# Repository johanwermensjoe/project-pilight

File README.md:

# project-pilight
An ambilight clone using Raspberry Pi.

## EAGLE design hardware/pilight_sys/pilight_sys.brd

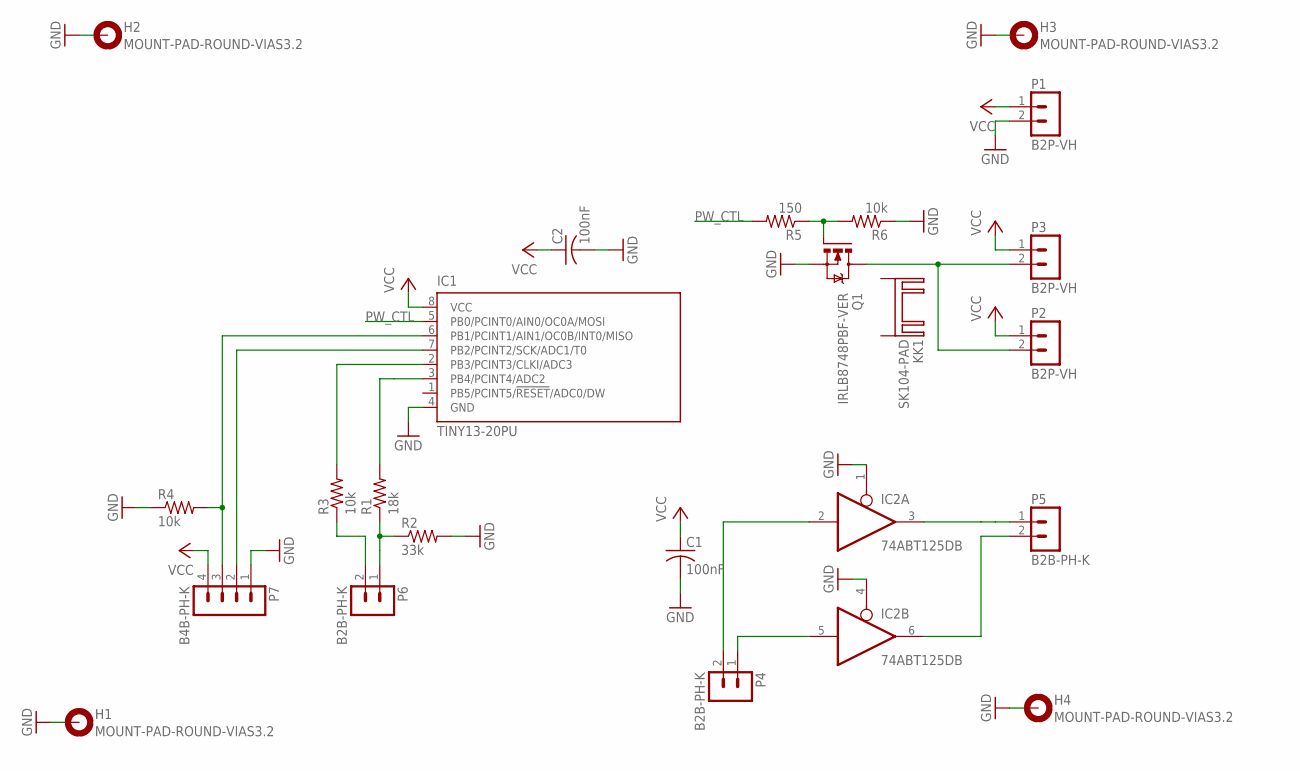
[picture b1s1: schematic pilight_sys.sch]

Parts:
C1, C2: 100nF; C0805
H1, H2, H3, H4: MOUNT-PAD-ROUND-VIAS3.2; 3,2-PAD
IC1: TINY13-20PU; DIL08
IC2: 74ABT125DB; SSOP14
KK1: SK104-PAD
P1, P2, P3: B2P-VH
P4, P5, P6: B2B-PH-K
P7: B4B-PH-K
Q1: IRLB8748PBF-VER; TO220AV
R1: 18k; R0805
R2: 33k; R0805
R3, R4, R6: 10k; R0805
R5: 150; R0805

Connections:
GND: C1.2, C2.2, H1.B3,2, H1.P$1, H1.P$2, H1.P$3, H1.P$4, H1.P$5, H1.P$6, H1.P$7, H1.P$8, H1.P$9, H2.B3,2, H2.P$1, H2.P$2, H2.P$3, H2.P$4, H2.P$5, H2.P$6, H2.P$7, H2.P$8, H2.P$9, H3.B3,2, H3.P$1, H3.P$2, H3.P$3, H3.P$4, H3.P$5, H3.P$6, H3.P$7, H3.P$8, H3.P$9, H4.B3,2, H4.P$1, H4.P$2, H4.P$3, H4.P$4, H4.P$5, H4.P$6, H4.P$7, H4.P$8, H4.P$9, IC1.4 (GND), IC2.1 (OE), IC2.4 (OE), IC2.7 (GND), P1.2, P7.1, Q1.S, R2.2, R4.1, R6.1
unnamed: IC2.5 (I), P4.1
unnamed: IC2.2 (I), P4.2
unnamed: IC2.3 (O), P5.1
unnamed: IC2.6 (O), P5.2
unnamed: P2.2, P3.2, Q1.D
unnamed: P6.1, R1.1, R2.1
unnamed: P6.2, R3.1
unnamed: IC1.6 (PB1/PCINT1/AIN1/OC0B/INT0/MISO), P7.3, R4.2
unnamed: Q1.G, R5.1, R6.2
unnamed: IC1.3 (PB4/PCINT4/ADC2), R1.2
unnamed: IC1.2 (PB3/PCINT3/CLKI/ADC3), R3.2
unnamed: IC1.7 (PB2/PCINT2/SCK/ADC1/T0), P7.2
PW_CTL: IC1.5 (PB0/PCINT0/AIN0/OC0A/MOSI), R5.2
VCC: C1.1, C2.1, IC1.8 (VCC), IC2.14 (VCC), P1.1, P2.1, P3.1, P7.4

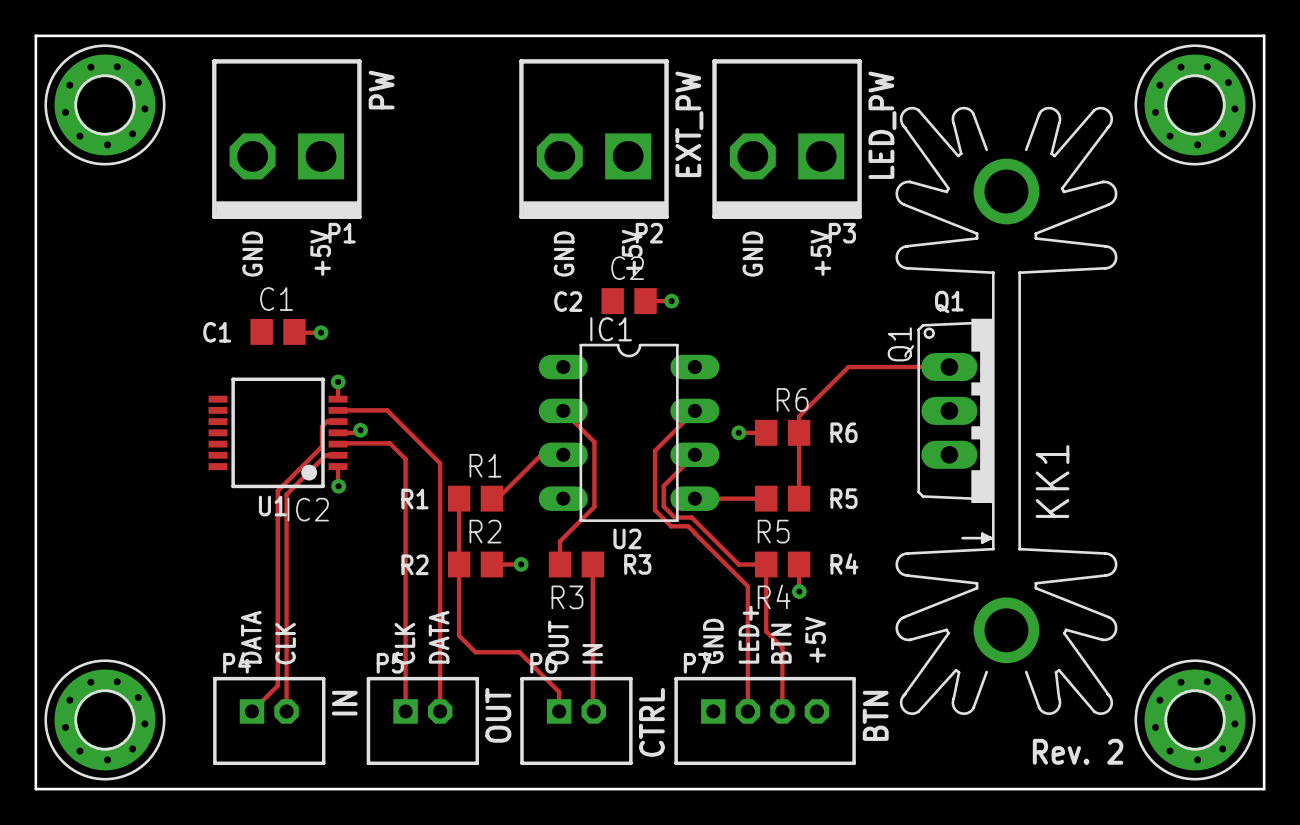
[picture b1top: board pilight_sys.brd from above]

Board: 2 copper layers, 71.1 x 43.6 mm, 23 parts (0 on the bottom side), 15 nets.

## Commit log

2015-10-04 Added schematic for level vonverter circuit.
2015-11-13 Updated schematics with added power circuit.
2015-12-19 Added base template for power circuit program.
2015-12-23 Finished power circuit code and design.
2015-12-25 Edited fritzing circuit.
2015-12-29 Changed power circuit ready signal to use rbpi txd GPIO pin.
2015-12-29 Renamed and moved files.
2015-12-29 Added python script for shutdown.
2015-12-30 Fixed python script.
2015-12-31 Improved fritzing design by adding ground terminal for button LED.
2016-01-06 Fixed missing Gnd connection.
2016-01-08 Added some signal redundancy to avoid shutdowns from noise.
2016-03-21 Added tools for config transfer and writing.
2016-10-20 Added remove of temp file in config_transf.
2019-01-06 Create schematic for circuit
2019-01-07 Finished v1 eagle designs
2019-02-17 Reorganize folder structure
2019-02-27 Update pinmap for power circuit program
2019-02-27 Update platformio config for new version
2019-02-28 Fix bug in circuit (3-state buffer)
2019-03-11 Update config_rewriter
2019-05-19 Update led config
2019-07-18 Update eagle files

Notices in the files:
parts and their libraries:
con-jst-vh: Copyright (C) 2016, Bob Starr
